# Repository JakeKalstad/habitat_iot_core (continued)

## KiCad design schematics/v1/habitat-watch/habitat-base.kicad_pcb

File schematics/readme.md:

# Schematics

Kicad Schematics for circuitry and PCB board design

## Kicad 

https://www.kicad.org/

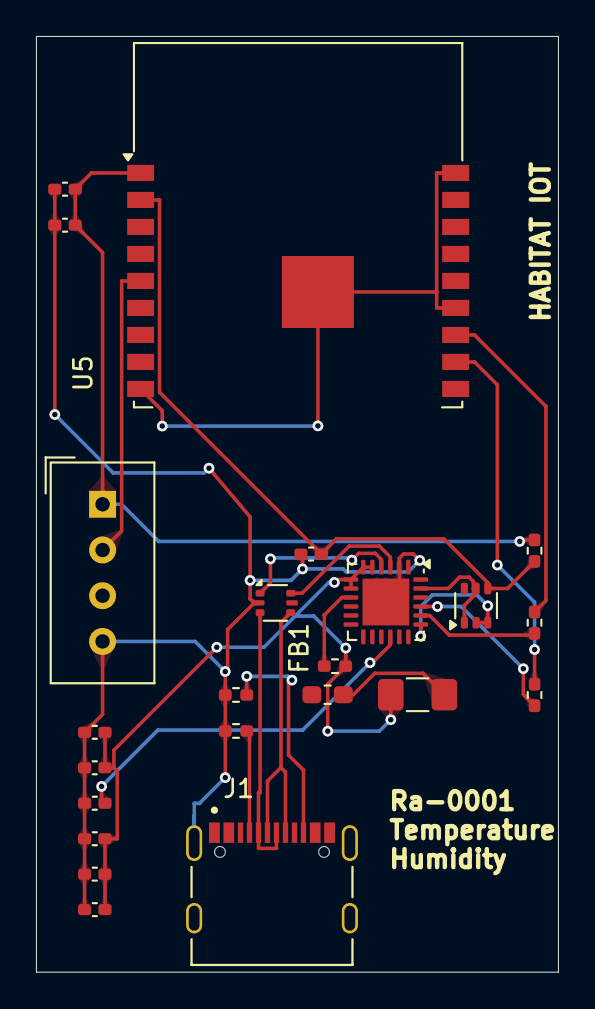
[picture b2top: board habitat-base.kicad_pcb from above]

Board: 2 copper layers, 29.0 x 52.0 mm, 23 parts (0 on the bottom side), 21 nets.

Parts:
C1, C5, C8: 22u; C_0402_1005Metric_Pad0.74x0.62mm_HandSolder
C2, C6, C7, C9: 100n; C_0402_1005Metric_Pad0.74x0.62mm_HandSolder
C3, C4: 4u7; C_0402_1005Metric_Pad0.74x0.62mm_HandSolder
F1: Polyfuse; Fuse_1206_3216Metric_Pad1.42x1.75mm_HandSolder
FB1: BLM21PG221; L_0603_1608Metric_Pad1.05x0.95mm_HandSolder
J1: USB_C; HRO_TYPE-C-31-M-12
Q1: UMH3N; SOT-363_SC-70-6
R1, R2: 5K1; R_0402_1005Metric_Pad0.72x0.64mm_HandSolder
R3, R6: 10K; R_0402_1005Metric_Pad0.72x0.64mm_HandSolder
R4, R5: 22R; R_0402_1005Metric_Pad0.72x0.64mm_HandSolder
U1: USBLC6-2P6; SOT-666
U3: CP2104; QFN-24-1EP_4x4mm_P0.5mm_EP2.6x2.6mm
U4: DHT11; Aosong_DHT11_5.5x12.0_P2.54mm
U5: ESP-WROOM-02

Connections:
+3.3V: C8.1, C9.1, R6.2, U4.1 (VDD), U5.1 (VDD)
+3.3VA: C1.1, C2.1, C3.1, C5.1, C6.1, F1.2, R3.2, U3.5 (VIO), U3.6 (VDD), U3.7 (REGIN), U3.8 (VBUS)
/DTR: Q1.1 (E1), Q1.5 (B2), U3.23 (~DTR)
/EN: C7.1, Q1.4 (E2), R6.1, U5.2 (EN)
/GPIO13: U4.2 (DATA), U5.5 (IO13)
/RTS: Q1.2 (B1), Q1.3 (C2), U3.19 (~RTS)
/RX: R4.1, U5.11 (RXD)
/TX: R5.1, U5.12 (TXD)
GND: C1.2, C2.2, C3.2, C4.2, C5.2, C6.2, C7.2, C8.2, C9.2, J1.S1 (SHIELD), R1.2, R2.2, U1.2 (GND), U3.2 (GND), U3.25 (GND), U4.4 (GND)
unnamed: F1.1, FB1.2
unnamed: J1.A5 (CC1), R1.1
unnamed: J1.B5 (CC2), R2.1
unnamed: J1.A6 (D+), J1.B6 (D+), U1.4 (I/O2)
unnamed: J1.A7 (D-), J1.B7 (D-), U1.3 (I/O2)
unnamed: U1.6 (I/O1), U3.3 (D+)
unnamed: U1.1 (I/O1), U3.4 (D-)
unnamed: R5.2, U3.20 (RXD)
unnamed: R4.2, U3.21 (TXD)
unnamed: C4.1, U3.16 (VPP)
unnamed: R3.1, U3.9 (~RST)
unnamed: U5.9 (GND), U5.13 (GND), U5.18 (GND), U5.19 (GND)

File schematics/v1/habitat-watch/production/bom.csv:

Designator,Footprint,Quantity,Value,LCSC Part #
"C1, C5, C8",0402,3,22u,
"C2, C6, C7, C9",0402,4,100n,
C3,0402,1,4u7,
F1,1206,1,Polyfuse,
FB1,0603,1,BLM21PG221,
J1,USB_C_Receptacle_HRO_TYPE-C-31-M-12,1,USB_C,
Q1,SOT-363_SC-70-6,1,UMH3N,
"R1, R2",0402,2,5K1,
"R3, R6",0402,2,10K,
"R4, R5",0402,2,22R,
U1,SOT-666,1,USBLC6-2P6,
U2,ESP32-WROOM-32D,1,ESP32-WROOM-32D,
U3,QFN-24-1EP_4x4mm_P0.5mm_EP2.6x2.6mm,1,CP2104,
U4,Aosong_DHT11_5.5x12.0_P2.54mm,1,DHT11,

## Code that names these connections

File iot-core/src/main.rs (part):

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pub mod networking;
pub mod servo;
use esp_idf_hal::gpio::{
    Gpio0, Gpio1, Gpio10, Gpio11, Gpio12, Gpio13, Gpio14, Gpio15, Gpio16, Gpio17, Gpio18, Gpio19,
    Gpio2, Gpio21, Gpio22, Gpio23, Gpio25, Gpio26, Gpio27, Gpio3, Gpio32, Gpio33, Gpio34, Gpio35,
    Gpio36, Gpio39, Gpio4, Gpio5, Gpio6, Gpio7, Gpio8, Gpio9, Pins,
};

static CONFIG_JSON: &str = include_str!("config.json");
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
static PRODUCT_CONFIGURATION_JSON: &str = include_str!("config.json");
enum GpioPin {
    Gpio0(Arc<Mutex<Gpio0>>),
    Gpio1(Arc<Mutex<Gpio1>>),
    Gpio2(Arc<Mutex<Gpio2>>),
    Gpio3(Arc<Mutex<Gpio3>>),
    Gpio4(Arc<Mutex<Gpio4>>),
    Gpio5(Arc<Mutex<Gpio5>>),
    Gpio6(Arc<Mutex<Gpio6>>),
    Gpio7(Arc<Mutex<Gpio7>>),
    Gpio8(Arc<Mutex<Gpio8>>),
    Gpio9(Arc<Mutex<Gpio9>>),
    Gpio10(Arc<Mutex<Gpio10>>),
    Gpio11(Arc<Mutex<Gpio11>>),
    Gpio12(Arc<Mutex<Gpio12>>),
    Gpio13(Arc<Mutex<Gpio13>>),
    Gpio14(Arc<Mutex<Gpio14>>),
    Gpio15(Arc<Mutex<Gpio15>>),
    Gpio16(Arc<Mutex<Gpio16>>),
    Gpio17(Arc<Mutex<Gpio17>>),
    Gpio18(Arc<Mutex<Gpio18>>),
    Gpio19(Arc<Mutex<Gpio19>>),
    Gpio21(Arc<Mutex<Gpio21>>),
    Gpio22(Arc<Mutex<Gpio22>>),
    Gpio23(Arc<Mutex<Gpio23>>),
    Gpio25(Arc<Mutex<Gpio25>>),
    Gpio26(Arc<Mutex<Gpio26>>),
    Gpio27(Arc<Mutex<Gpio27>>),
    Gpio32(Arc<Mutex<Gpio32>>),
    Gpio33(Arc<Mutex<Gpio33>>),
    Gpio34(Arc<Mutex<Gpio34>>),
    Gpio35(Arc<Mutex<Gpio35>>),
    Gpio36(Arc<Mutex<Gpio36>>),
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
    let mut gpio_map: HashMap<i32, Arc<Mutex<AnyIOPin>>> = HashMap::new();

    gpio_map.insert(0, Arc::new(Mutex::new(pins.gpio0.into())));
    gpio_map.insert(1, Arc::new(Mutex::new(pins.gpio1.into())));
    #[cfg(not(feature = "display"))]
    gpio_map.insert(2, Arc::new(Mutex::new(pins.gpio2.into())));
    gpio_map.insert(3, Arc::new(Mutex::new(pins.gpio3.into())));
    #[cfg(not(feature = "display"))]
    gpio_map.insert(4, Arc::new(Mutex::new(pins.gpio4.into())));
    gpio_map.insert(5, Arc::new(Mutex::new(pins.gpio5.into())));
    gpio_map.insert(6, Arc::new(Mutex::new(pins.gpio6.into())));
    gpio_map.insert(7, Arc::new(Mutex::new(pins.gpio7.into())));
    gpio_map.insert(8, Arc::new(Mutex::new(pins.gpio8.into())));
    gpio_map.insert(9, Arc::new(Mutex::new(pins.gpio9.into())));
    gpio_map.insert(10, Arc::new(Mutex::new(pins.gpio10.into())));
    gpio_map.insert(11, Arc::new(Mutex::new(pins.gpio11.into())));
    gpio_map.insert(12, Arc::new(Mutex::new(pins.gpio12.into())));
    #[cfg(not(feature = "display"))]
    gpio_map.insert(13, Arc::new(Mutex::new(pins.gpio13.into())));
    gpio_map.insert(14, Arc::new(Mutex::new(pins.gpio14.into())));
    #[cfg(not(feature = "display"))]
    gpio_map.insert(15, Arc::new(Mutex::new(pins.gpio15.into())));
    gpio_map.insert(16, Arc::new(Mutex::new(pins.gpio16.into())));
    gpio_map.insert(17, Arc::new(Mutex::new(pins.gpio17.into())));
    #[cfg(not(feature = "display"))]
    gpio_map.insert(18, Arc::new(Mutex::new(pins.gpio18.into())));
    gpio_map.insert(19, Arc::new(Mutex::new(pins.gpio19.into())));
    // gpio_map.insert(20, Arc::new(Mutex::new(pins.gpio20.into())));
    gpio_map.insert(21, Arc::new(Mutex::new(pins.gpio21.into())));
    gpio_map.insert(22, Arc::new(Mutex::new(pins.gpio22.into())));
    #[cfg(not(feature = "display"))]
    gpio_map.insert(23, Arc::new(Mutex::new(pins.gpio23.into())));
    // gpio_map.insert(27, Arc::new(Mutex::new(pins.gpio27.into())));

    #[cfg(feature = "display")]
    use esp_idf_hal::spi::SpiDriver;

    #[cfg(feature = "display")]
    let mut pcd_rst = pins.gpio2;
    #[cfg(feature = "display")]
    let mut pcd_dc = pins.gpio4;
    #[cfg(feature = "display")]
    let mut pcd_light = pins.gpio13;
    #[cfg(feature = "display")]
    let mut pcd_cs = pins.gpio15;
    #[cfg(feature = "display")]
    let mut pcd_clk = pins.gpio18;
    #[cfg(feature = "display")]
    let mut pcd_din = pins.gpio23;

    #[cfg(feature = "display")]
    let dc_pin_driver = PinDriver::input_output(pcd_dc).expect("Get dc pin driver");
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    };

    #[cfg(feature = "motor")]
    let in1 = PinDriver::output(pins.gpio26).unwrap();
    #[cfg(feature = "motor")]
    let in2 = PinDriver::output(pins.gpio25).unwrap();
    #[cfg(feature = "motor")]
    let timer_driver = LedcTimerDriver::new(
        peripherals.ledc.timer0,
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    )
    .expect("Get timer");
#[cfg(feature = "motor")]
    let driver = LedcDriver::new(peripherals.ledc.channel0, timer_driver, pins.gpio27)
        .expect("get ledc driver");
    #[cfg(feature = "motor")]
    let mut motor = l298n::Motor::new(in1, in2, driver);
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    #[cfg(feature = "water_sensor")]
    let water_sensor_adc1 = AdcDriver::new(peripherals.adc1).expect("calibrated");

    let mut p32 = pins.gpio32;
    let mut p33 = pins.gpio33;
    let mut iter = 0;
    //.write_string(display).expect("Failed to write string");

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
